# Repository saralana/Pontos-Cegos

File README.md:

# PONTOS CEGOS
# 	Ferramenta para mapeamento de pontos cegos não atingidos por câmeras de segurança
#	| ARDUINO | RASPBERRY | GPS | SD | Sensor IR |

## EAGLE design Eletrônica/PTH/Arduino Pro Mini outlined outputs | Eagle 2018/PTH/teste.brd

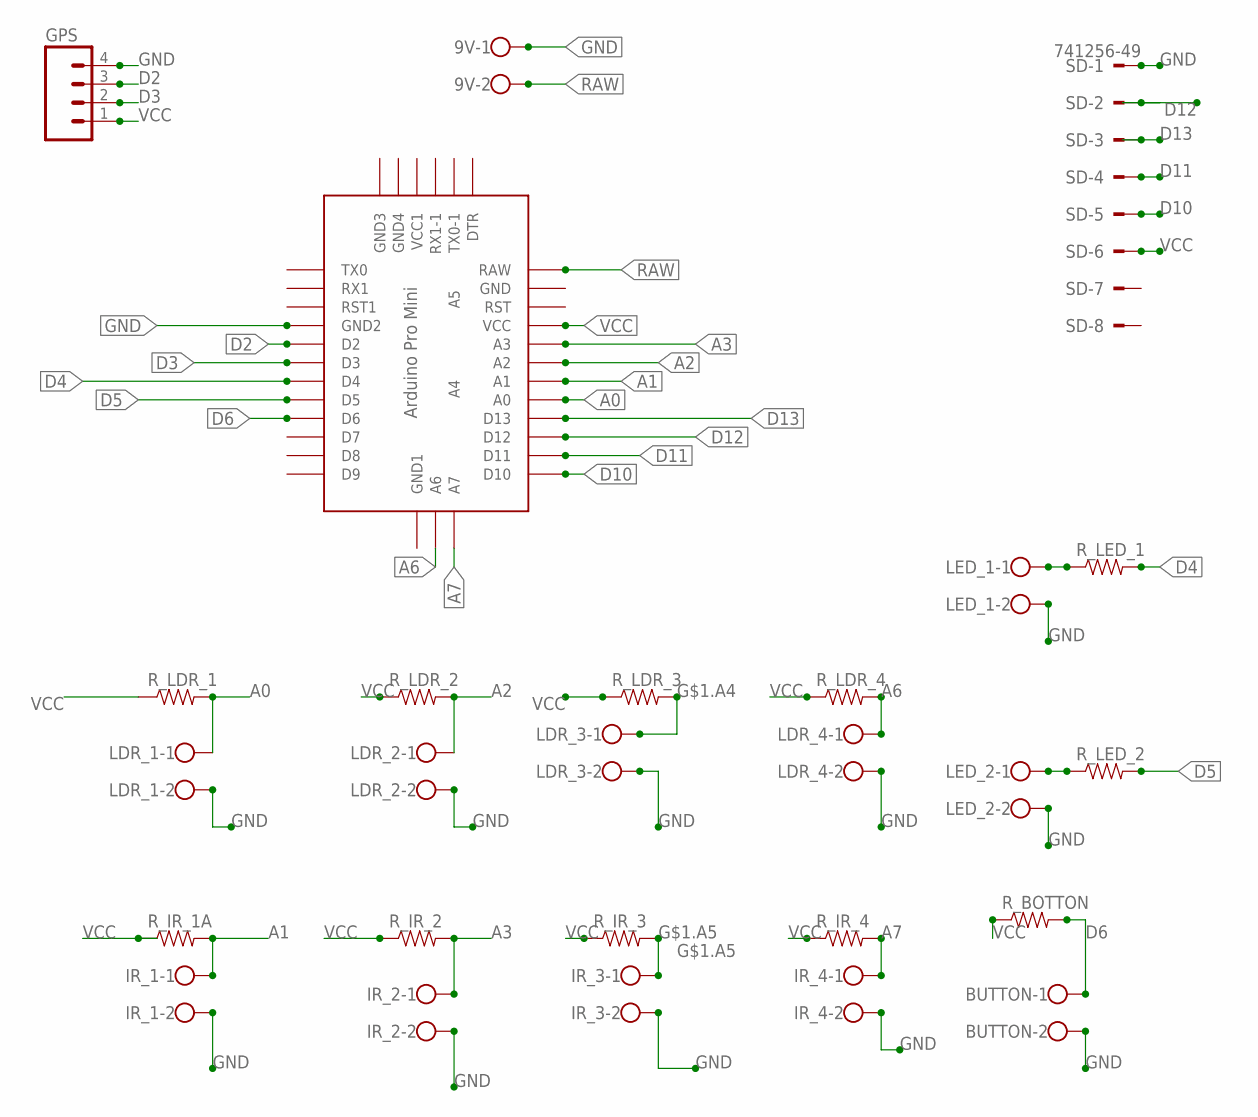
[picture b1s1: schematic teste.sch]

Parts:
9V: W237-102
BUTTON: W237-102
GPS: M04LONGPADS; 1X04_LONGPADS
IR_1, IR_2, IR_3, IR_4: W237-102
LDR_1, LDR_2, LDR_3, LDR_4: W237-102
LED_1, LED_2: W237-102
R_BOTTON: RESISTORAXIAL-0.3; AXIAL-0.3
R_IR_1A, R_IR_2, R_IR_3, R_IR_4: RESISTORAXIAL-0.3; AXIAL-0.3
R_LDR_1, R_LDR_2, R_LDR_3, R_LDR_4: RESISTORAXIAL-0.3; AXIAL-0.3
R_LED_1, R_LED_2: RESISTORAXIAL-0.3; AXIAL-0.3
SD: 741256-49
U$2: ABK-PRO-MINI

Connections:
A0: LDR_1.1, R_LDR_1.P$2 (2), U$2.A0
A1: IR_1.1, R_IR_1A.P$2 (2), U$2.A1
A2: LDR_2.1, R_LDR_2.P$2 (2), U$2.A2
A3: IR_2.1, R_IR_2.P$2 (2), U$2.A3
A6: LDR_4.1, R_LDR_4.P$2 (2), U$2.A6
A7: IR_4.1, R_IR_4.P$2 (2), U$2.A7
D2: GPS.3, U$2.D2
D3: GPS.2, U$2.D3
D4: R_LED_1.P$2 (2), U$2.D4
D5: R_LED_2.P$2 (2), U$2.D5
D6: BUTTON.1, R_BOTTON.P$2 (2), U$2.D6
D10: SD.5, U$2.D10
D11: SD.4, U$2.D11
D12: SD.2, U$2.D12
D13: SD.3, U$2.D13
G$1.A4: LDR_3.1, R_LDR_3.P$2 (2)
G$1.A5: IR_3.1, R_IR_3.P$2 (2)
GND: 9V.1, BUTTON.2, GPS.4, IR_1.2, IR_2.2, IR_3.2, IR_4.2, LDR_1.2, LDR_2.2, LDR_3.2, LDR_4.2, LED_1.2, LED_2.2, SD.1, U$2.GND1 (GND2)
unnamed: LED_1.1, R_LED_1.P$1 (1)
unnamed: LED_2.1, R_LED_2.P$1 (1)
RAW: 9V.2, U$2.RAW
VCC: GPS.1, R_BOTTON.P$1 (1), R_IR_1A.P$1 (1), R_IR_2.P$1 (1), R_IR_3.P$1 (1), R_IR_4.P$1 (1), R_LDR_1.P$1 (1), R_LDR_2.P$1 (1), R_LDR_3.P$1 (1), R_LDR_4.P$1 (1), SD.6, U$2.VCC

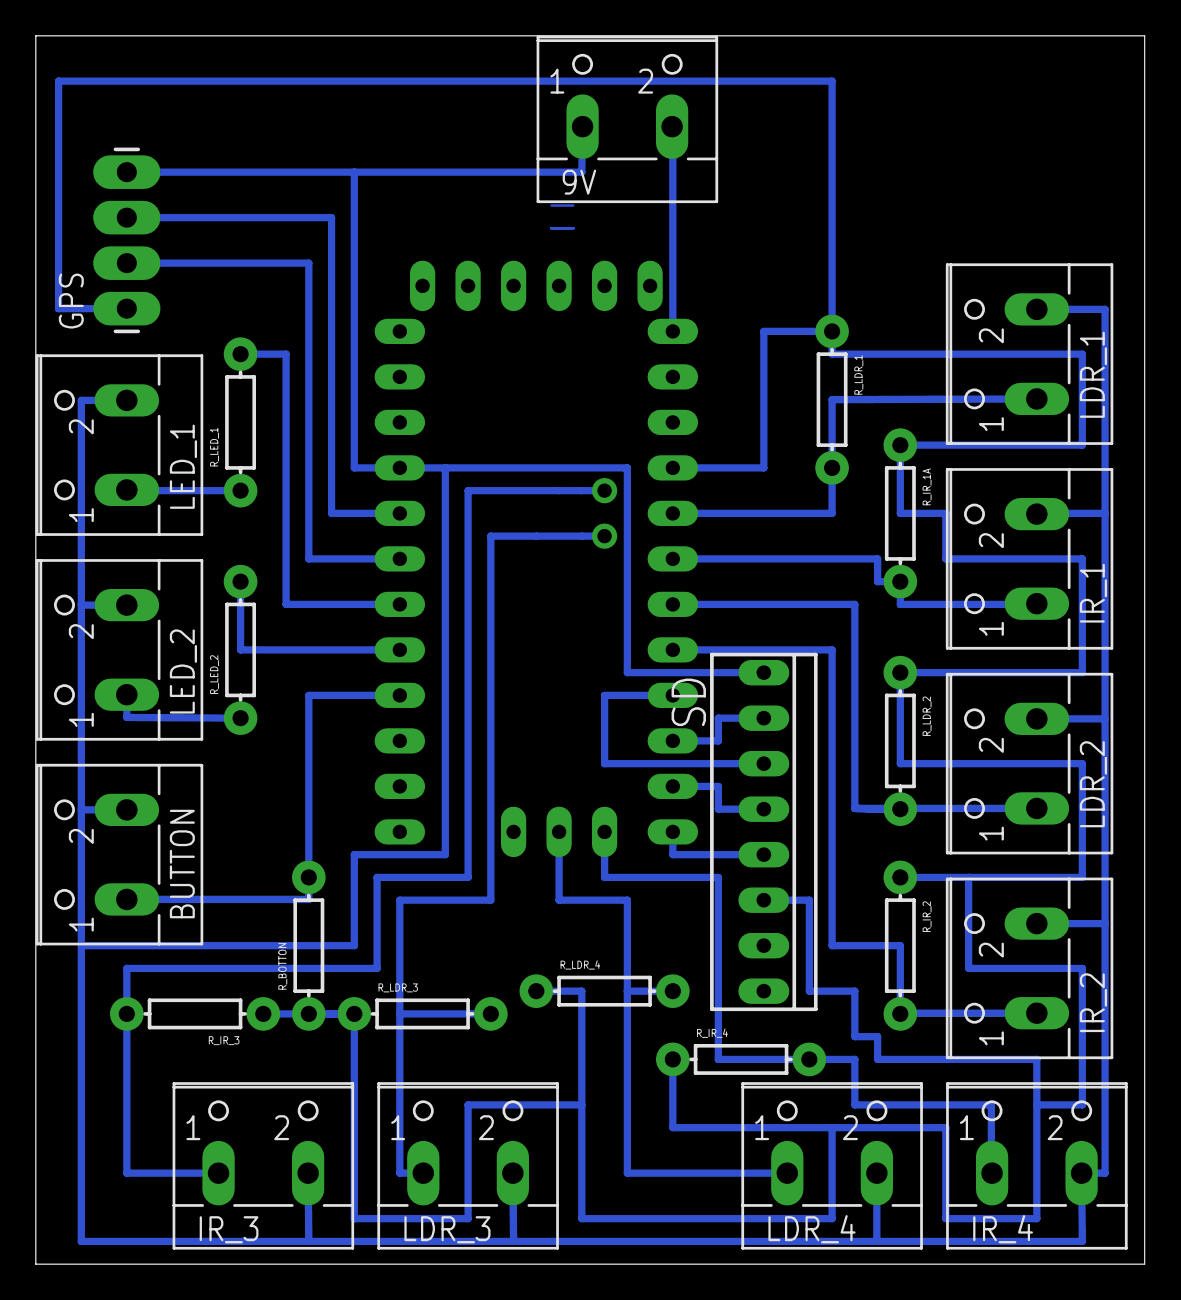
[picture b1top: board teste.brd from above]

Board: 2 copper layers, 61.9 x 68.6 mm, 26 parts (0 on the bottom side), 22 nets.

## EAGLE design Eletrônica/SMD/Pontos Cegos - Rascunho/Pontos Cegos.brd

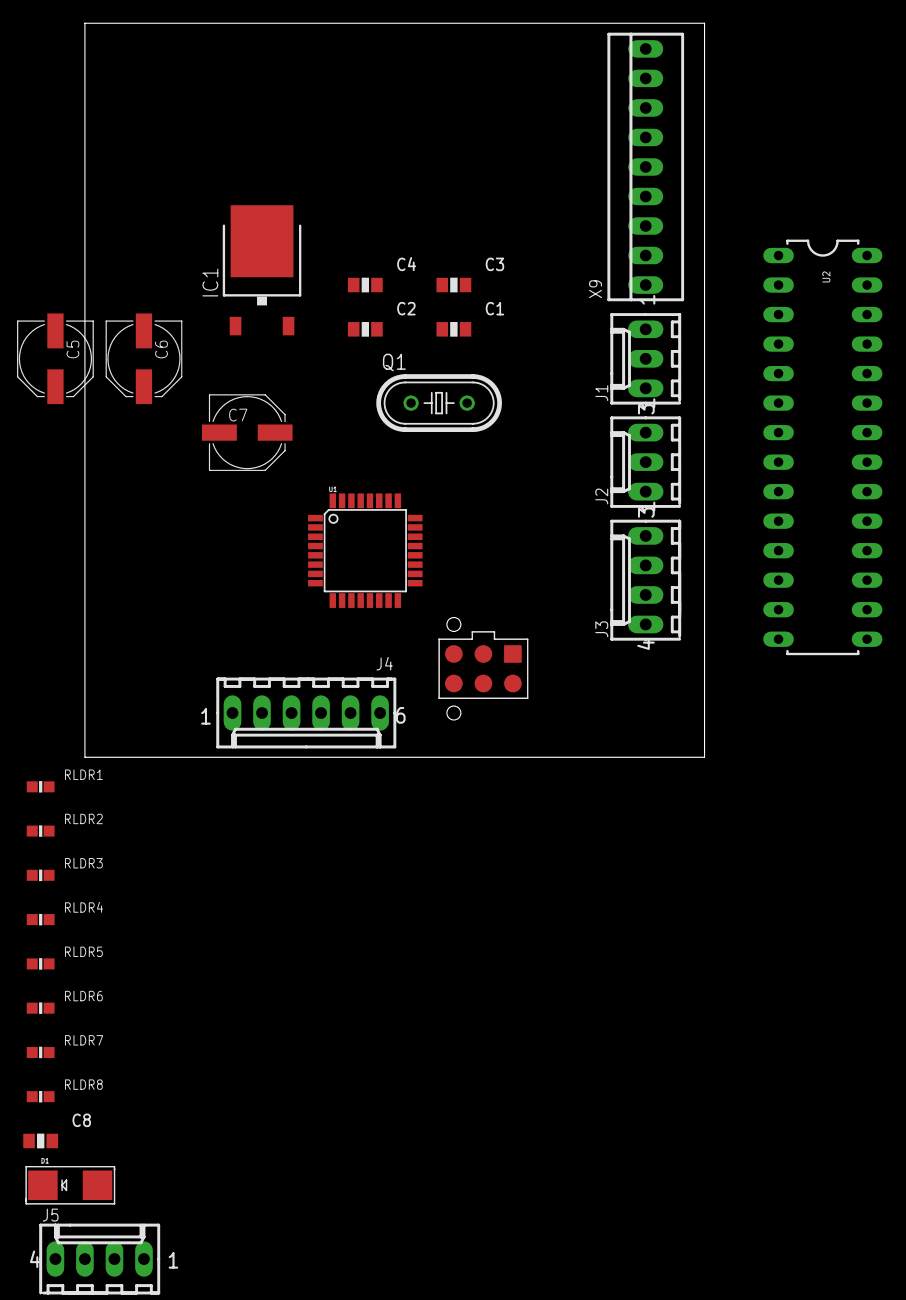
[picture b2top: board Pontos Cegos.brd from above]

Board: 2 copper layers, 53.3 x 63.2 mm, 28 parts (0 on the bottom side), 17 nets, no tracks yet.

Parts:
C1, C2, C3, C4, C8: C0805
C5, C6, C7: PANASONIC_D
D1: SMADIODE
IC1: 7806DT; TO252
J1, J2: 22-27-2031-03; 6410-03
J3, J5: 22-27-2041-04; 6410-04
J4: 22-27-2061-06; 6410-06
Q1: HC49U-V
RLDR1, RLDR2, RLDR3, RLDR4, RLDR5, RLDR6, RLDR7, RLDR8: R0603
U1: ATMEGA328P; TQFP32-08
U2: ATMEGA328P_PDIP; DIL28-3
U$1: ISP_POGOISP_POGO; ISP_POGO
X9: 22-23-2091

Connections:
+5V: C3.1, C4.1, C8.1, RLDR1.1, RLDR2.1, RLDR3.1, RLDR4.1, RLDR5.1, RLDR6.1, RLDR7.1, RLDR8.1, U1.4, U1.6, U1.18, U1.20, U$1.VCC
A0: RLDR1.2, U1.23, X9.2
A1: RLDR2.2, U1.24, X9.3
A2: RLDR3.2, U1.25, X9.4
A3: RLDR4.2, U1.26, X9.5
A4: RLDR5.2, U1.27, X9.6
A5: RLDR6.2, U1.28, X9.7
A6: RLDR7.2, U1.19, X9.8
A7: RLDR8.2, U1.22, X9.9
GND: C1.2, C2.2, C3.2, C4.2, C5.-, C6.-, C7.-, C8.2, IC1.3, U1.3, U1.5, U1.21, U$1.GND, X9.1
MISO: U1.16, U$1.MISO
MOSI: U1.15, U$1.MOSI
unnamed: C1.1, Q1.2, U1.7
unnamed: C2.1, Q1.1, U1.8
unnamed: C5.+, C6.+, D1.C, IC1.1
unnamed: C7.+, D1.A, IC1.2
SCK: U1.17, U$1.SCK

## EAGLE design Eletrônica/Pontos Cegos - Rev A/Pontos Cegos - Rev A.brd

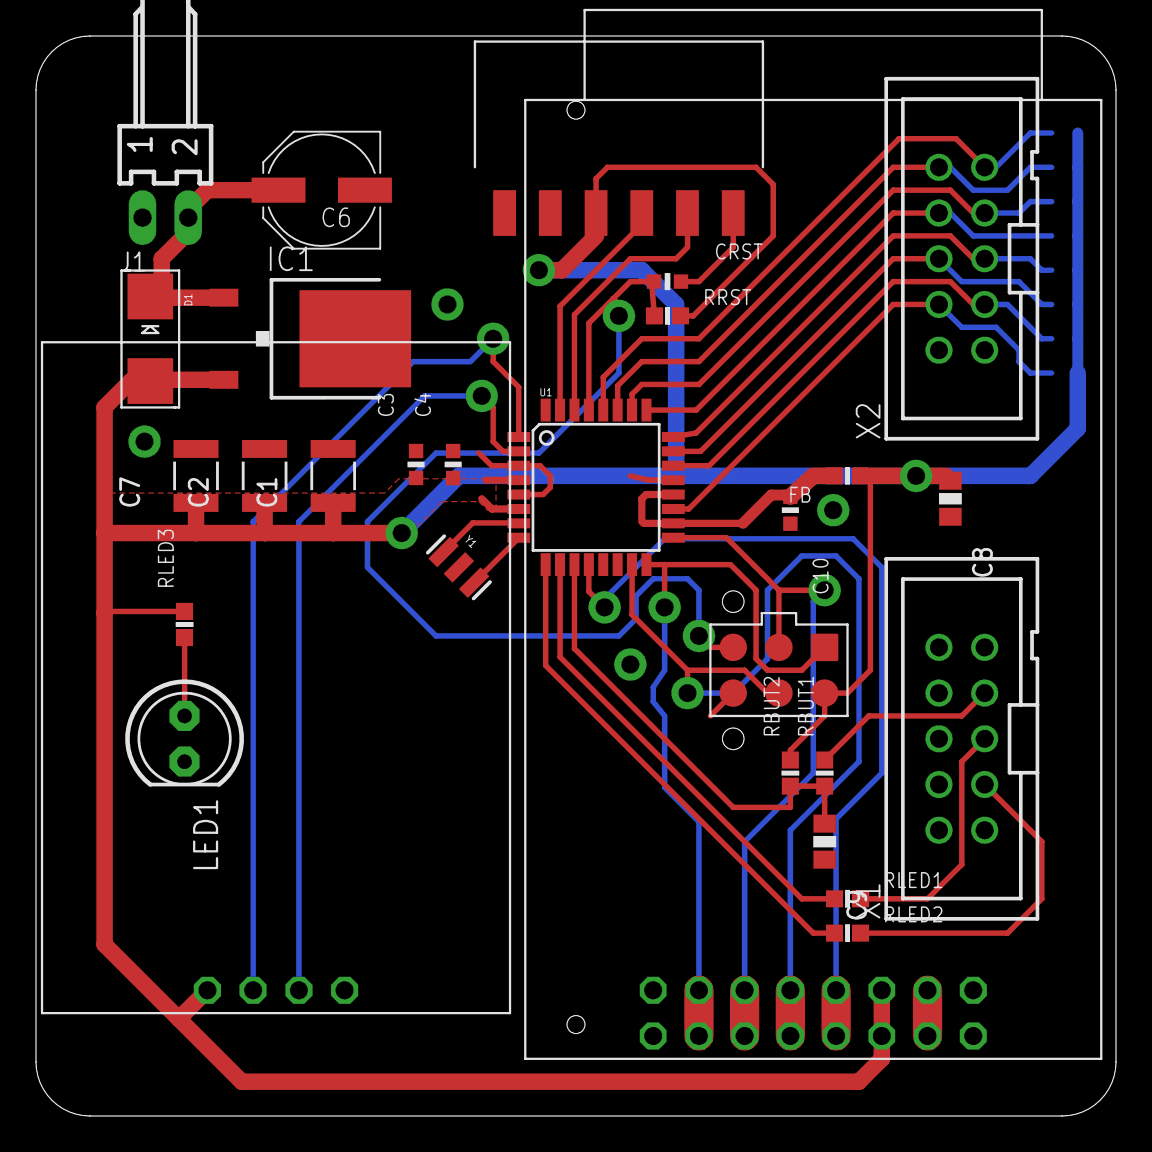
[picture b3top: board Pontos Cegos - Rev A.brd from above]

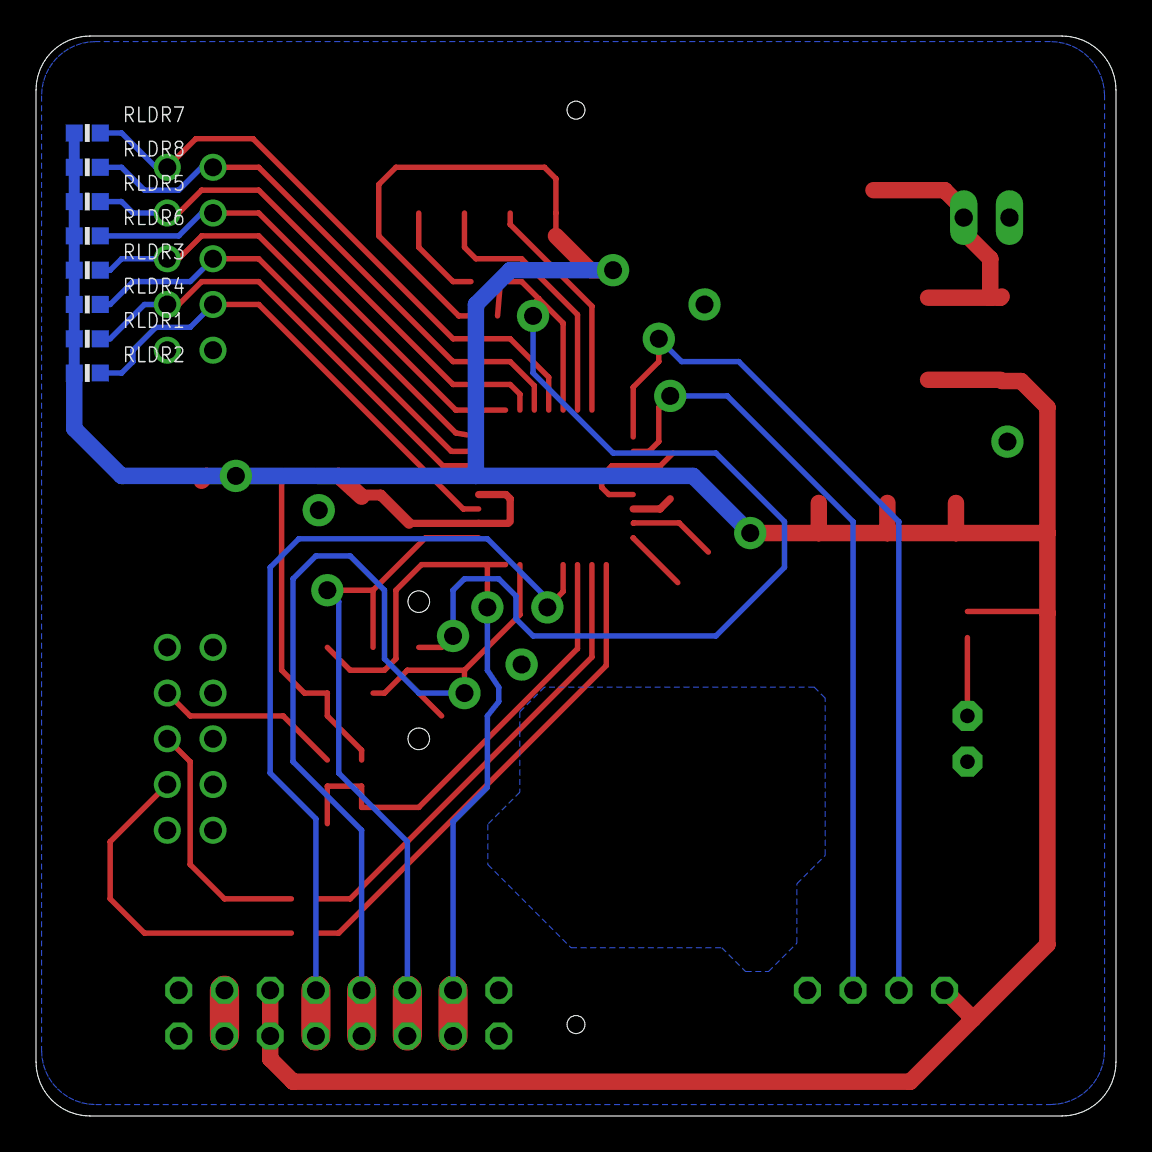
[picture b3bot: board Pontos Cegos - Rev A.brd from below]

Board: 2 copper layers, 60.0 x 60.0 mm, 37 parts (8 on the bottom side), 32 nets.

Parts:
C1, C2, C7: C1210
C3, C4, C10: C0603
C6: PANASONIC_D
C8, C9: C0805
CRST: C0603
D1: SMADIODE
FB: R0603
IC1: 7806DT; TO252
J1: 22-05-7028-02; 7395-02
LED1: LED5MM
RBUT1, RBUT2: R0603
RLDR1, RLDR2, RLDR3, RLDR4, RLDR5, RLDR6, RLDR7, RLDR8: R0603
RLED1, RLED2, RLED3: R0603
RRST: R0603
U1: ATMEGA328P; TQFP32-08
U$1: ISP_POGOISP_POGO; ISP_POGO
U$2: SD_BREAKOUT
U$3: NEO6M_BREAKOUT
U$4: FTDI_HEADERSMD; FTDI_HEADER_SMD
X1, X2: 2510-; PAK100/2500-10
Y1: 16MHz; RESONATOR-SMD

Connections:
+5V: C1.1, C2.1, C3.1, C4.1, C7.1, C8.1, D1.A, FB.1, IC1.2, RBUT2.2, RLDR1.1, RLDR2.1, RLDR3.1, RLDR4.1, RLDR5.1, RLDR6.1, RLDR7.1, RLDR8.1, RLED3.2, RRST.2, U1.4, U1.6, U$1.VCC, U$2.P$6, U$2.P$14, U$3.VCC, U$4.VCC
A0: RLDR4.2, U1.23, X2.6
A1: RLDR3.2, U1.24, X2.5
A2: RLDR6.2, U1.25, X2.8
A3: RLDR5.2, U1.26, X2.7
A4: RLDR8.2, U1.27, X2.10
A5: RLDR7.2, U1.28, X2.9
A6: RLDR2.2, U1.19, X2.4
A7: RLDR1.2, U1.22, X2.3
BUT_IN: RBUT1.2, X1.7
D5: RLED2.1, U1.9
D6: RLED1.1, U1.10
D7: C9.1, RBUT1.1, RBUT2.1, U1.11
D8: U1.12, U$2.P$5, U$2.P$13
DTR: CRST.2, U$4.DTR
GND: C1.2, C2.2, C3.2, C4.2, C6.-, C7.2, C8.2, C9.2, C10.2, IC1.3, J1.1, LED1.K, U1.3, U1.5, U1.21, U$1.GND, U$2.P$1, U$2.P$8, U$2.P$9, U$2.P$16, U$3.GND, U$4.GND, X1.1, X1.2, X1.4, X1.6, X1.8, X1.10, X2.1, X2.2, Y1.2
LED1: RLED1.2, X1.5
LED2: RLED2.2, X1.3
MISO: U1.16, U$1.MISO, U$2.P$2, U$2.P$10
MOSI: U1.15, U$1.MOSI, U$2.P$4, U$2.P$12
unnamed: U1.7, Y1.1
unnamed: U1.8, Y1.3
unnamed: LED1.A, RLED3.1
unnamed: C6.+, D1.C, IC1.1, J1.2
unnamed: C10.1, FB.2, U1.18, U1.20
unnamed: U$2.P$7, U$2.P$15
RST: CRST.1, RRST.1, U1.29, U$1.RST
RX: U1.30, U$4.RX
SCK: U1.17, U$1.SCK, U$2.P$3, U$2.P$11
SOFT_RX: U1.2, U$3.TX
SOFT_TX: U1.1, U$3.RX
TX: U1.31, U$4.TX

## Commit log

2016-09-10 Reorganizing, Electronics added
2016-09-10 Fixed untracked files
2016-09-10 Firmware
2016-09-10 Paraboloide | IR
2016-09-10 Bill of Materials added
2016-09-13 BRD updated
2016-09-15 Calibracao | IR | LDR
2016-09-16 BOM updated
2016-09-25 Mecanica Capacete
2016-09-25 Codigo Modificado para Arduino Pro Mini
2016-09-25 Esquematico e PCB | Projeto PTH
2016-09-25 GERBER PCB | Projeto PTH
2016-09-25 Melhoramentos no Código
2016-09-26 Firmware para 4 sensores
2016-09-28 Sensores Calibrados
2016-09-28 Sensores Calibrados | 4
2018-03-02 New Schematic, Board and Gerbers for arduinos pro mini with outlined outputs
2018-03-02 Classes documentation
2018-03-02 folder

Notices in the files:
parts and their libraries:
SparkFun-Connectors: Licensing: Creative Commons ShareAlike 4.0 International - https://creativecommons.org/licenses/by-sa/4.0
SparkFun-DigitalIC: Licensing: CC v3.0 Share-Alike You are welcome to use this library for commercial purposes.
